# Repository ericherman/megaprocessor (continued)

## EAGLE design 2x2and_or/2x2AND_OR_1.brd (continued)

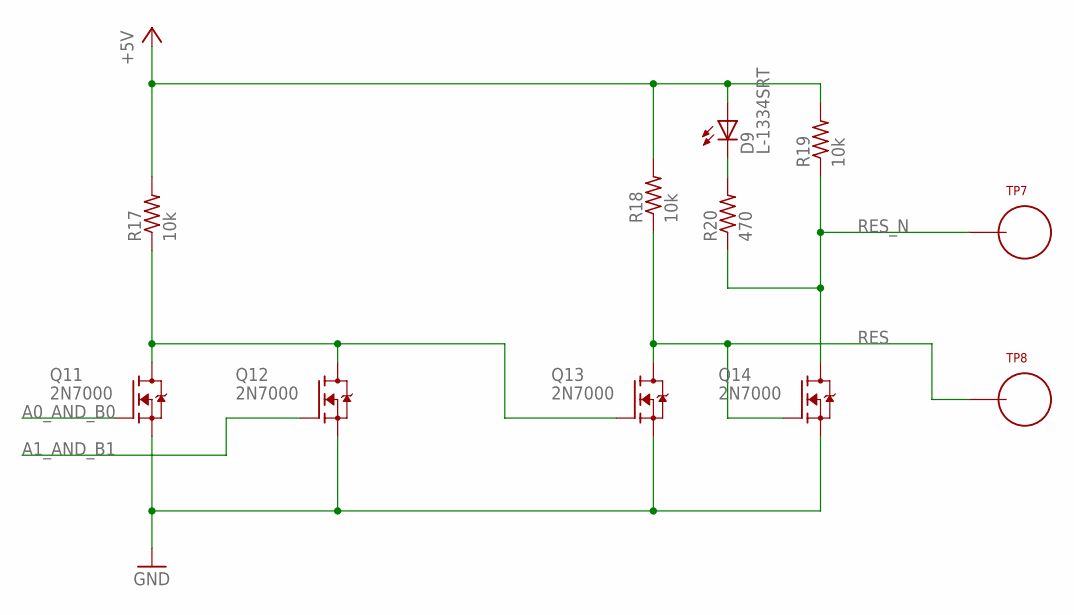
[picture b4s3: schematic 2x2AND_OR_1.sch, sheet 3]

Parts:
D9: L-1334SRT; LED3MM
Q11, Q12, Q13, Q14: 2N7000; TO92-DGS
R17, R18, R19: 10k; R_P2INCH
R20: 470; R_P2INCH
TP7, TP8: TEST_LOOP

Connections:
+5V: D9.A, R17.2, R18.2, R19.2; also elsewhere on the board
A0_AND_B0: Q11.G; also elsewhere on the board
A1_AND_B1: Q12.G; also elsewhere on the board
GND: Q11.S, Q12.S, Q13.S, Q14.S; also elsewhere on the board
unnamed: Q11.D, Q12.D, Q13.G, R17.1
unnamed: D9.K (C), R20.2
RES: Q13.D, Q14.G, R18.1, TP8.P$1
RES_N: Q14.D, R19.1, R20.1, TP7.P$1

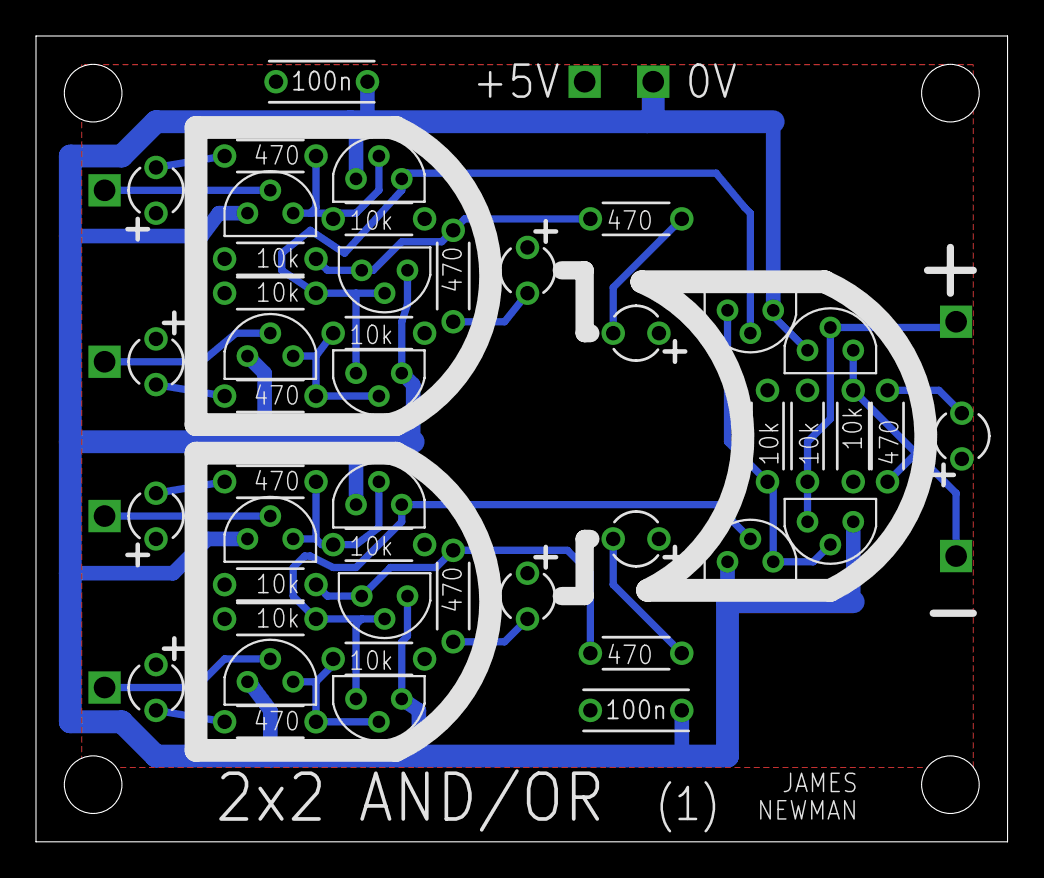
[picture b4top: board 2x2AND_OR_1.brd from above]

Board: 2 copper layers, 54.0 x 44.8 mm, 57 parts (0 on the bottom side), 26 nets.
